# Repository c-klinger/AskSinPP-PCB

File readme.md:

# AskSin++ PSB
Collection of my PCBs for building Homebrew devices using [AskSin++](https://github.com/pa-pa/AskSinPP).

## HB-UNI-328P
soon...

## HB-UNI-328P-SMALL
Flexible and small (49x49mm) PCB for AskSin++ devices with multiple power options. Small enough to fit into devices that integrate into german wall socket / switch series.

[Schematics](https://github.com/c-klinger/AskSinPP-PCB/blob/main/hb-uni-328p-small/hb-uni-328p-small.pdf)

### Bill of Material

| Pos | References | Description | Value | Size | Quantity | Order Links \* | Notes |
|-----|------------|-------------|-------|------|----------|-------------|-------|
| 01 | U1 | ATmega328P(B) |  | TQFP-32 | 1 | [Reichelt](https://www.reichelt.de/8-bit-atmega-avr-mikrocontroller-32-kb-20-mhz-tqfp-32-atmega-328pb-au-p269093.html), [Aliexpress](https://s.click.aliexpress.com/e/_DmFgvzj) | |
| 02 | U2 | CC1101 Module |  |  | 1 | [Aliexpress](https://s.click.aliexpress.com/e/_DnFmipB) | |
| 03 | U3 | MAX1724EZK33 | | SOT-23 | 1 | [Mouser](https://www.mouser.de/ProductDetail/Analog-Devices-Maxim-Integrated/MAX1724EZK33%2bT?qs=1THa7WoU59ExxSPMjwY5Kw%3D%3D),  [Aliexpress](https://s.click.aliexpress.com/e/_DEjlEQt) | Only for Poweroption 1
| 04 | U4 | HT7533 | | SOT-89 | 1 | [ELV](https://de.elv.com/spannungsregler-33v-ht-7533-1-smd-sot-89-056535),  [Aliexpress](https://s.click.aliexpress.com/e/_Dkyk1p7)  | Only for Poweroption 2
| 05 | Q1 | IRLML6244 | | SOT-23 | 1 | [Reichelt](https://www.reichelt.de/mosfet-n-kanal-20-v-6-3-a-rds-on-0-021-ohm-sot-23-irlml-6244-p132145.html), [Aliexpress](https://s.click.aliexpress.com/e/_DmmdQxj) | only for Poweroption 1 
| 06 | Q2 | IRLML5203 | | SOT-23 | 1 | [Reichelt](https://www.reichelt.de/mosfet-p-kanal-30-v-3-a-rds-on-0-098-ohm-sot-23-irlml-5203-p108740.html), [Aliexpress](https://s.click.aliexpress.com/e/_DmmdQxj) | only for Poweroption 2 
| 07 | C1, C6, C8, C10, C11 | Capacitor | 10uF | 1206 | 4 (max) | [Reichelt](https://www.reichelt.de/ch/de/vielschicht-kerko-10-f-16v-125-c-kem-x7r1206-10u-p207163.html),  [Aliexpress](https://s.click.aliexpress.com/e/_DCrWg7b) | C8 for Poweroption 1, C10 + C11 for Poweroption 2
| 08 | C2, C7, C5 | Capacitor | 100nF | 1206 | 3 | [Reichelt](https://www.reichelt.de/smd-vielschicht-keramikkondensator-100n-10--x7r-g1206-100n-p22889.html),  [Aliexpress](https://s.click.aliexpress.com/e/_DCrWg7b) | |
| 09 | C3, C4 | Capacitor | 9-12pF | 1206 | 2 | [Reichelt](https://www.reichelt.de/vielschicht-kerko-1206-10-pf-5-cog-50-v-125-c-ve-4k-npo-g1206-10p-p31885.html), [Aliexpress](https://s.click.aliexpress.com/e/_DCrWg7b) | |
| 10 | C9  | Capacitor | 33nF | 1206 | 1 | [Reichelt](https://www.reichelt.de/smd-vielschicht-keramikkondensator-33n-10--x7r-g1206-33n-p22890.html), [Aliexpress](https://s.click.aliexpress.com/e/_DCrWg7b) | only for Poweroption 1 |
| 11 | C12  | Electrolytic Capacitor | 1000uF |  | 1 | [Reichelt](https://www.reichelt.de/elko-1000-f-50v-105-c-rad-lxz-50-1k0-p166432.html), [Aliexpress](https://s.click.aliexpress.com/e/_DCrWg7b) | only for Poweroption 2 |
| 12 | C13  | Capacitor | 10nF | 1206 | 1 | [Reichelt](https://www.reichelt.de/vielschicht-kerko-1206-10-nf-10-x7r-50-v-125-c-x7r-g1206-10n-p31897.html), [Aliexpress](https://s.click.aliexpress.com/e/_DCrWg7b) |  | 
| 13 | D1 | Dual LED | | 3mm | 1 | [Reichelt](https://www.reichelt.de/ch/de/led-3-mm-tht-3-pin-rot-gruen-627-565-nm-40-40-mcd-60--kbt-l-115wegw-p231039.html), [Aliexpress](https://s.click.aliexpress.com/e/_DFd0iCd) |  |
| 14 | F1 | Fuse (PTC) | 6V, 250mA | 1206 | 1 | [Aliexpress](https://s.click.aliexpress.com/e/_DEQvumh) | for Poweroption 1 |
|    | F1 | Fuse (PTC) | 16V, 250mA | 1206 | 1 | [Reichelt](https://www.reichelt.de/ptc-sicherung-smd-1206-16v-350ma-rueckstellend-ptc-fsmd0351206--p279338.html), [Aliexpress](https://s.click.aliexpress.com/e/_DEQvumh) | for Poweroption 2 |
| 15 | J3 | Pin Header 2.54mm |  | 2x1 | 1 | [Reichelt](https://www.reichelt.de/ch/de/stiftleisten-2-54-mm-1x02-gerade-mpe-087-1-002-p119879.html), [Aliexpress](https://s.click.aliexpress.com/e/_Dl2TPCt) | optional |
| 16 | J4 | Pin Header 2.54mm |  | 6x1 | 1 | [Reichelt](https://www.reichelt.de/ch/de/stiftleisten-2-54-mm-1x06-gerade-mpe-087-1-006-p119883.html), [Aliexpress](https://s.click.aliexpress.com/e/_Dl2TPCt) | optional |
| 17 | J5 | Pin Header 2.54mm |  | 3x2 | 1 | [Reichelt](https://www.reichelt.de/ch/de/stiftleisten-2-54-mm-2x03-gerade-mpe-087-2-006-p119893.html), [Aliexpress](https://s.click.aliexpress.com/e/_DFoS9I5) | optional |
| 18 | J6 | Pin Header 2.54mm |  | 4x1 | 1 | [Reichelt](https://www.reichelt.de/ch/de/stiftleisten-2-54-mm-1x04-gerade-mpe-087-1-004-p119881.html), [Aliexpress](https://s.click.aliexpress.com/e/_Dl2TPCt) | optional|
| 19 | L1 | Induction Coil | 10UH | 4x3mm| 1| [Conrad](https://www.conrad.de/de/p/murata-lqh43cn100k03l-lqh43cn100k03l-induktivitaet-smd-1812-10-h-0-65-a-1-st-537082.html) [Aliexpress](https://s.click.aliexpress.com/e/_DFXlwZn) |only for Poweroption 1 |
| 10 | R1, R2 | Resistor | 330 | 1206 | 2 | [Richelt](https://www.reichelt.de/ch/de/smd-widerstand-1206-330-ohm-250-mw-1--vis-crcw1206330-p238114.html), [Aliexpress](https://s.click.aliexpress.com/e/_DDa77BX) |  |
| 21 | R3, R8, R9 | Resistor | 10K | 1206 | 3 | [Reichelt](https://www.reichelt.de/ch/de/smd-widerstand-1206-10-kohm-250-mw-5--smd-1-4w-10k-p18244.html) [Aliexpress](https://s.click.aliexpress.com/e/_DDa77BX) |  |
| 22 | R4 | Resistor | 470K | 1206 | 1 | [Reichelt](https://www.reichelt.de/ch/de/smd-widerstand-1206-470-kohm-250-mw-5--smd-1-4w-470k-p18338.html), [Aliexpress](https://s.click.aliexpress.com/e/_DDa77BX) |  |
| 23 | R5, R6, R7 | Resistor | 100K | 1206 | 3 (max) | [Reichelt](https://www.reichelt.de/ch/de/smd-widerstand-1206-100-kohm-250-mw-5--smd-1-4w-100k-p18243.html), [Aliexpress](https://s.click.aliexpress.com/e/_DDa77BX) | R7 for Poweroption 2 only |
| 24 | SW1, SW2 | Tactile Switch | | 6x3mm | 2 | [Aliexpress](https://s.click.aliexpress.com/e/_DlZyH0Z) | |
| 25 | Y1 |  SMD Crystal | 32.768 KHz | 3.8x8mm | 1 | [Reichelt](https://www.reichelt.de/ch/de/keramik-smd-quarz-8-7-x-3-7-x-2-5-mm-32-768-khz-iqd-lfxtal003000-p245481.html), [Aliexpress](https://s.click.aliexpress.com/e/_Dn3q3Az) | |

\* *I have not tested all parts using this order links, no guarantee that every linked component works. Aliexpress links are affiliate links, so i will get a small commission when you order using this link. This will help me with further projects. Thanks.*

### Comments
* Minimum size of SMD components is 1206: it's possible to solder the PCB by hand.
* 3 Power Options
    * Poweroption 1: Step-Up DC-DC Converter MAX1724EZK33: 0.8V to 5.5V Input Voltage Range. Best for Battery powered devices.
    * Poweroption 2: Linear Voltage Regulators (LDO) HT7533: 5-12V Input Voltage Range. Best for most external DC Power Supply. Jumper J2 needs to be shortened for this Poweroption. 
    * Poweroption 3: External 3.3V Supply. Jumper J1 and J2 needs to be shortened this Poweroption. No fuse or reverse polarity protection!
* Assembly and use only one of the Power Options at time.

Inspired from pa-pa [HMSensor](https://github.com/pa-pa/HMSensor) and [HB-UNI-644](https://github.com/alexreinert/PCB#hb-uni-644-rev-2) from alexreinert. Thanks for your work.

# LICENSE

All content in this repository is is licensed under a [Creative Commons Attribution-NonCommercial-ShareAlike 4.0 International license](https://creativecommons.org/licenses/by-nc-sa/4.0/).

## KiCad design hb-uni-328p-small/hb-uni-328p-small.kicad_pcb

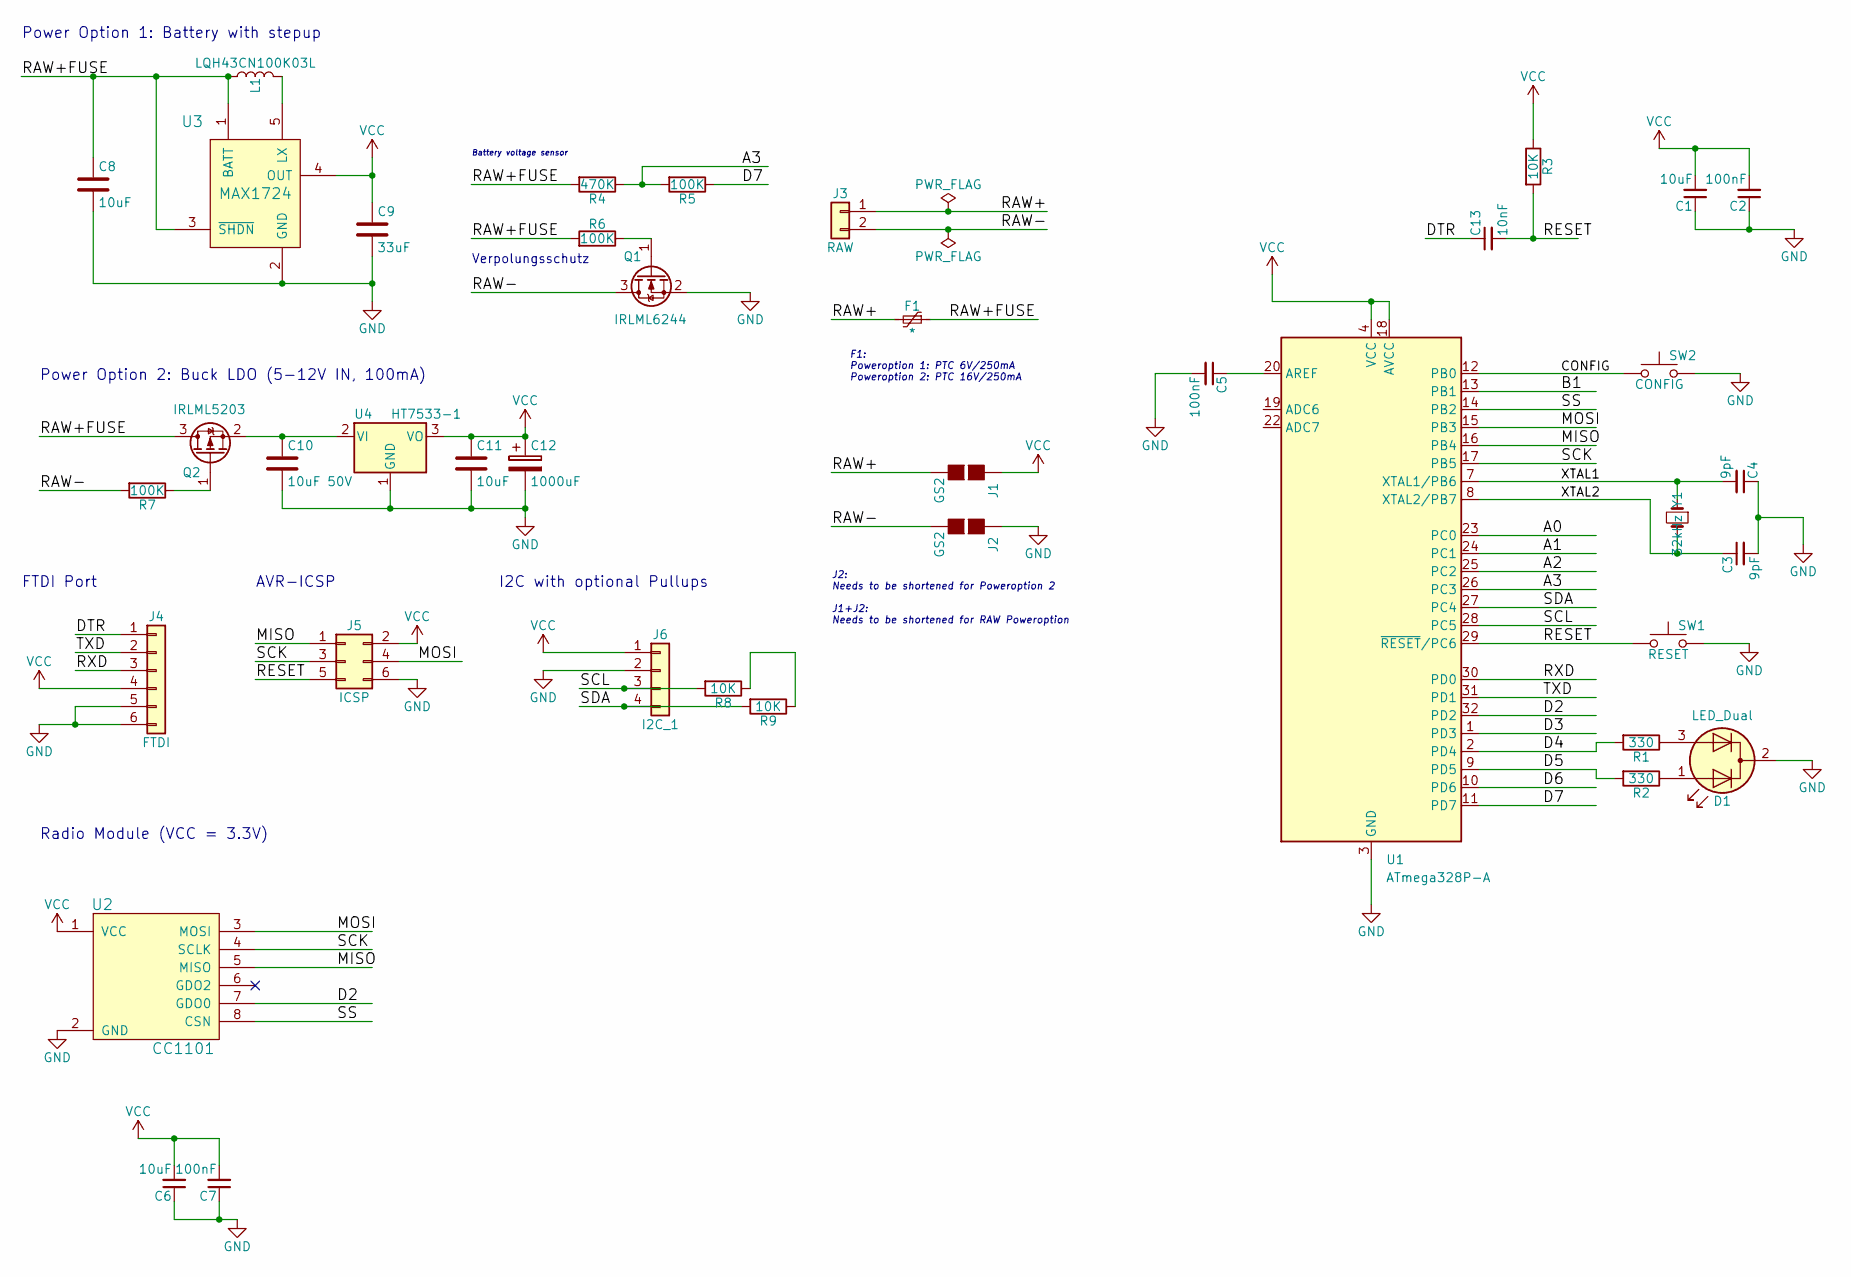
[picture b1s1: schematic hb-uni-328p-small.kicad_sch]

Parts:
C1, C6, C8, C11: 10uF; C_1206_3216Metric_Pad1.33x1.80mm_HandSolder
C2, C5, C7: 100nF; C_1206_3216Metric_Pad1.33x1.80mm_HandSolder
C3, C4: 9pF; C_1206_3216Metric_Pad1.33x1.80mm_HandSolder
C9: 33uF; C_1206_3216Metric_Pad1.33x1.80mm_HandSolder
C10: 10uF 50V; C_1206_3216Metric_Pad1.33x1.80mm_HandSolder
C12: 1000uF; CP_Radial_D10.0mm_P5.00mm
C13: 10nF; C_1206_3216Metric_Pad1.33x1.80mm_HandSolder
D1: LED_Dual; LED_D3.0mm-3
F1: *; R_1206_3216Metric_Pad1.30x1.75mm_HandSolder
J1, J2: GS2; SolderJumper-2_P1.3mm_Open_Pad1.0x1.5mm
J3: RAW; PinHeader_1x02_P2.54mm_Vertical
J4: FTDI; PinHeader_1x06_P2.54mm_Vertical
J5: ICSP; PinHeader_2x03_P2.54mm_Vertical
J6: I2C_1; PinHeader_1x04_P2.54mm_Vertical
L1: LQH43CN100K03L; L_1812_4532Metric_Pad1.30x3.40mm_HandSolder
Q1: IRLML6244; SOT-23_Handsoldering
Q2: IRLML5203; SOT-23_Handsoldering
R1, R2: 330; R_1206_3216Metric_Pad1.30x1.75mm_HandSolder
R3, R8, R9: 10K; R_1206_3216Metric_Pad1.30x1.75mm_HandSolder
R4: 470K; R_1206_3216Metric_Pad1.30x1.75mm_HandSolder
R5, R6, R7: 100K; R_1206_3216Metric_Pad1.30x1.75mm_HandSolder
SW1: RESET; SW_SPST_FSMSM
SW2: CONFIG; SW_SPST_FSMSM
U1: ATmega328P-A; TQFP-32_7x7mm_P0.8mm
U2: CC1101; CC1101-868MHz-Module
U3: MAX1724; TSOT-23-5_HandSoldering
U4: HT7533-1; SOT-89-3_Handsoldering
Y1: 32kHz; Crystal_SMD_0603-4Pin_6.0x3.5mm_HandSoldering

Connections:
/A0: U1.23 (PC0)
/A1: U1.24 (PC1)
/A2: U1.25 (PC2)
/A3: R4.1, R5.2, U1.26 (PC3)
/B1: U1.13 (PB1)
/CONFIG: SW2.1, U1.12 (PB0)
/D2: U1.32 (PD2), U2.7 (GDO0)
/D3: U1.1 (PD3)
/D4: R1.2, U1.2 (PD4)
/D5: R2.2, U1.9 (PD5)
/D6: U1.10 (PD6)
/D7: R5.1, U1.11 (PD7)
/DTR: C13.1, J4.1
/MISO: J5.1, U1.16 (PB4), U2.5 (MISO)
/MOSI: J5.4, U1.15 (PB3), U2.3 (MOSI)
/RAW+: F1.2, J1.2 (G2), J3.1
/RAW+FUSE: C8.1, F1.1, L1.1, Q2.3 (D), R4.2, R6.2, U3.1 (BATT), U3.3 (~SHDN)
/RAW-: J2.2 (G2), J3.2, Q1.3 (D), R7.2
/RESET: C13.2, J5.5, R3.2, SW1.1, U1.29 (~RESET/PC6)
/RXD: J4.3, U1.30 (PD0)
/SCK: J5.3, U1.17 (PB5), U2.4 (SCLK)
/SCL: J6.3, R8.2, U1.28 (PC5)
/SDA: J6.4, R9.2, U1.27 (PC4)
/SS: U1.14 (PB2), U2.8 (CSN)
/TXD: J4.2, U1.31 (PD1)
/XTAL1: C4.2, U1.7 (XTAL1/PB6), Y1.1
/XTAL2: C3.1, U1.8 (XTAL2/PB7), Y1.4
GND: C1.1, C2.1, C3.2, C4.1, C5.2, C6.1, C7.1, C8.2, C9.2, C10.2, C11.2, C12.2, D1.2 (K), J2.1 (G1), J4.5, J4.6, J5.6, J6.2, Q1.2 (S), SW1.2, SW2.2, U1.3 (GND), U1.5 (GND), U1.21 (GND), U2.2 (GND), U3.2 (GND), U4.1 (GND)
unnamed: C5.1, U1.20 (AREF)
unnamed: C10.1, Q2.2 (S), U4.2 (VI)
unnamed: D1.1 (A1), R2.1
unnamed: D1.3 (A2), R1.1
unnamed: L1.2, U3.5 (LX)
unnamed: Q1.1 (G), R6.1
unnamed: Q2.1 (G), R7.1
unnamed: R8.1, R9.1
VCC: C1.2, C2.2, C6.2, C7.2, C9.1, C11.1, C12.1, J1.1 (G1), J4.4, J5.2, J6.1, R3.1, U1.4 (VCC), U1.6 (VCC), U1.18 (AVCC), U2.1 (VCC), U3.4 (OUT), U4.3 (VO)

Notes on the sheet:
Radio Module (VCC = 3.3V)
AVR-ICSP
Battery voltage sensor
Verpolungsschutz
FTDI Port
Power Option 1: Battery with stepup
Power Option 2: Buck LDO (5-12V IN, 100mA)
J2: Needs to be shortened for Poweroption 2 J1+J2: Needs to be shortened for RAW Poweroption
I2C with optional Pullups
F1: Poweroption 1: PTC 6V/250mA Poweroption 2: PTC 16V/250mA

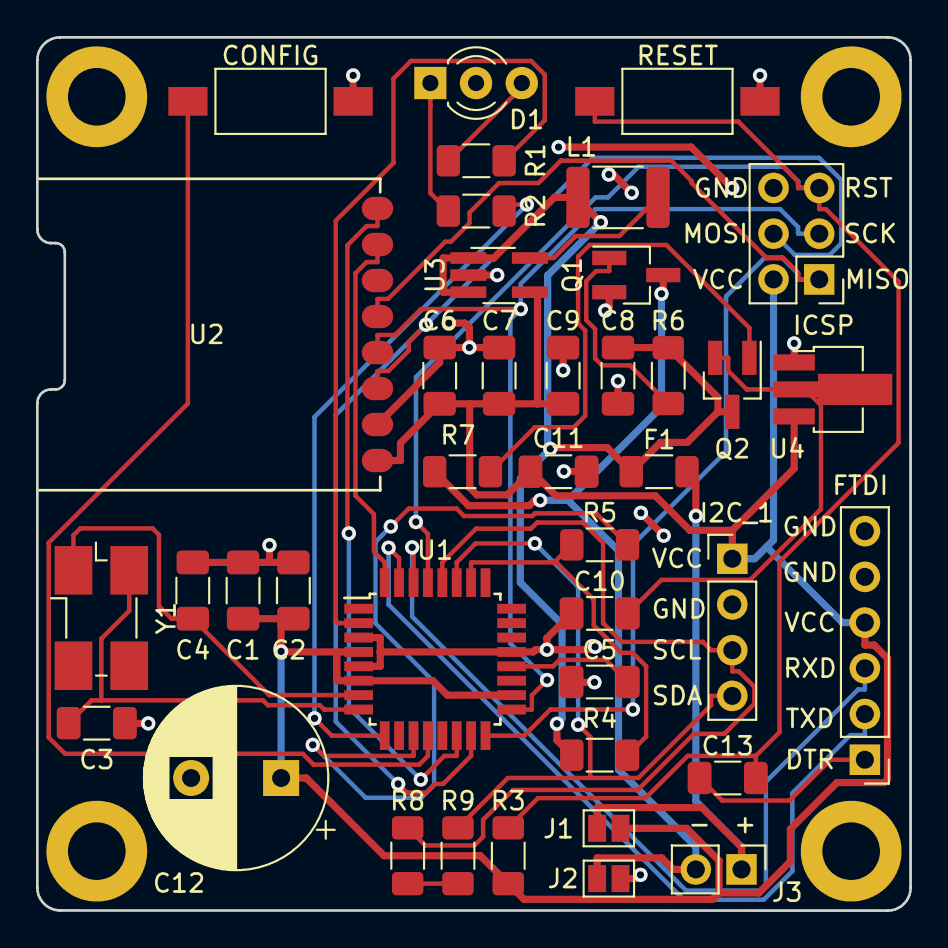
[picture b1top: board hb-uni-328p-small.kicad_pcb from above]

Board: 2 copper layers, 48.5 x 48.5 mm, 44 parts (0 on the bottom side), 31 nets.

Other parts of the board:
REF2, REF4, REF6, REF7: MountingHole_3.2mm_M3_DIN965_Pad

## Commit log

2023-04-30 Initial commit, HB-UNI-328P-SMALL
2023-04-30 fixed image in readme.md
2023-04-30 fixed schematics link in readme
2023-04-30 License
2023-04-30 readme, added links

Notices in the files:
hb-uni-328p-small/hb-uni-328p-small.kicad_pcb:
(C) 2023 chrisklinger.de
